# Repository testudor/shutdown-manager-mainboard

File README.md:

# Shutdown Manager Mainboard

This is a board for switching the AC mains input in machines such as 3D printers or CNC machines.

It is designed to be controlled by a push button switch with built-in dual color LEDs. An on-board LED driver controls these LEDs and different light patterns indicate the current system status.

The board has connections for two "nodes". These are external devices that require a safe shutdown procedure, such as a Raspberry Pi. It will trigger a shutdown of the nodes and will not turn off the power until they have completely shut down.

It is specifically designed to handle high inrush currents from SMPSs, which can cause normal relays to have their contacts weld together.

## I/O

### Nodes

| Pin | Function                                                                                     |
|-----|----------------------------------------------------------------------------------------------|
| NSD | Node Shutdown - is repeatedly cycled low and high to trigger a shutdown of external devices  |
| NHB | Node Heart Beat - should be driven HIGH, when a node is running and LOW when it's shut down. |

For an easy way to connect a Raspberry Pi see [this repo.](https://github.com/testudor/shutdown-manager-rpi-node)

### Push button switch

| Pin     | Function                                   |
|---------|--------------------------------------------|
| SW-/SW+ | Connected to the power switch.             |
| LD1/LD2 | Connected to the switches' dual color LED. |

I can recommend the ONPOW GQ19F-10E/RG/12/S, however any push button switch with 12V dual color LEDs should work. By dual color I mean LEDs which change their color based on polarity.

## Assembly

All necessary files can be found in the release section. They are compatible with the usual fab houses.

To use the full 16A this board was designed for, get 2oz PCBs or liberally coat the mains voltage traces on the bottom in solder.

I'm leaving these instructions intentionally vague as this is *NOT* a beginner's project. The more experienced should know what to do.

## Firmware

This board requires firmware to be flashed and configured. For details see [this repo.](https://github.com/testudor/shutdown-manager-firmware)

## Disclaimer

**WARNING:**

This board was designed to the best of my knowledge, but I am *NOT* an electrical engineer. If you decide to build this, I am not liable for damages or harm to yourself or anyone else.

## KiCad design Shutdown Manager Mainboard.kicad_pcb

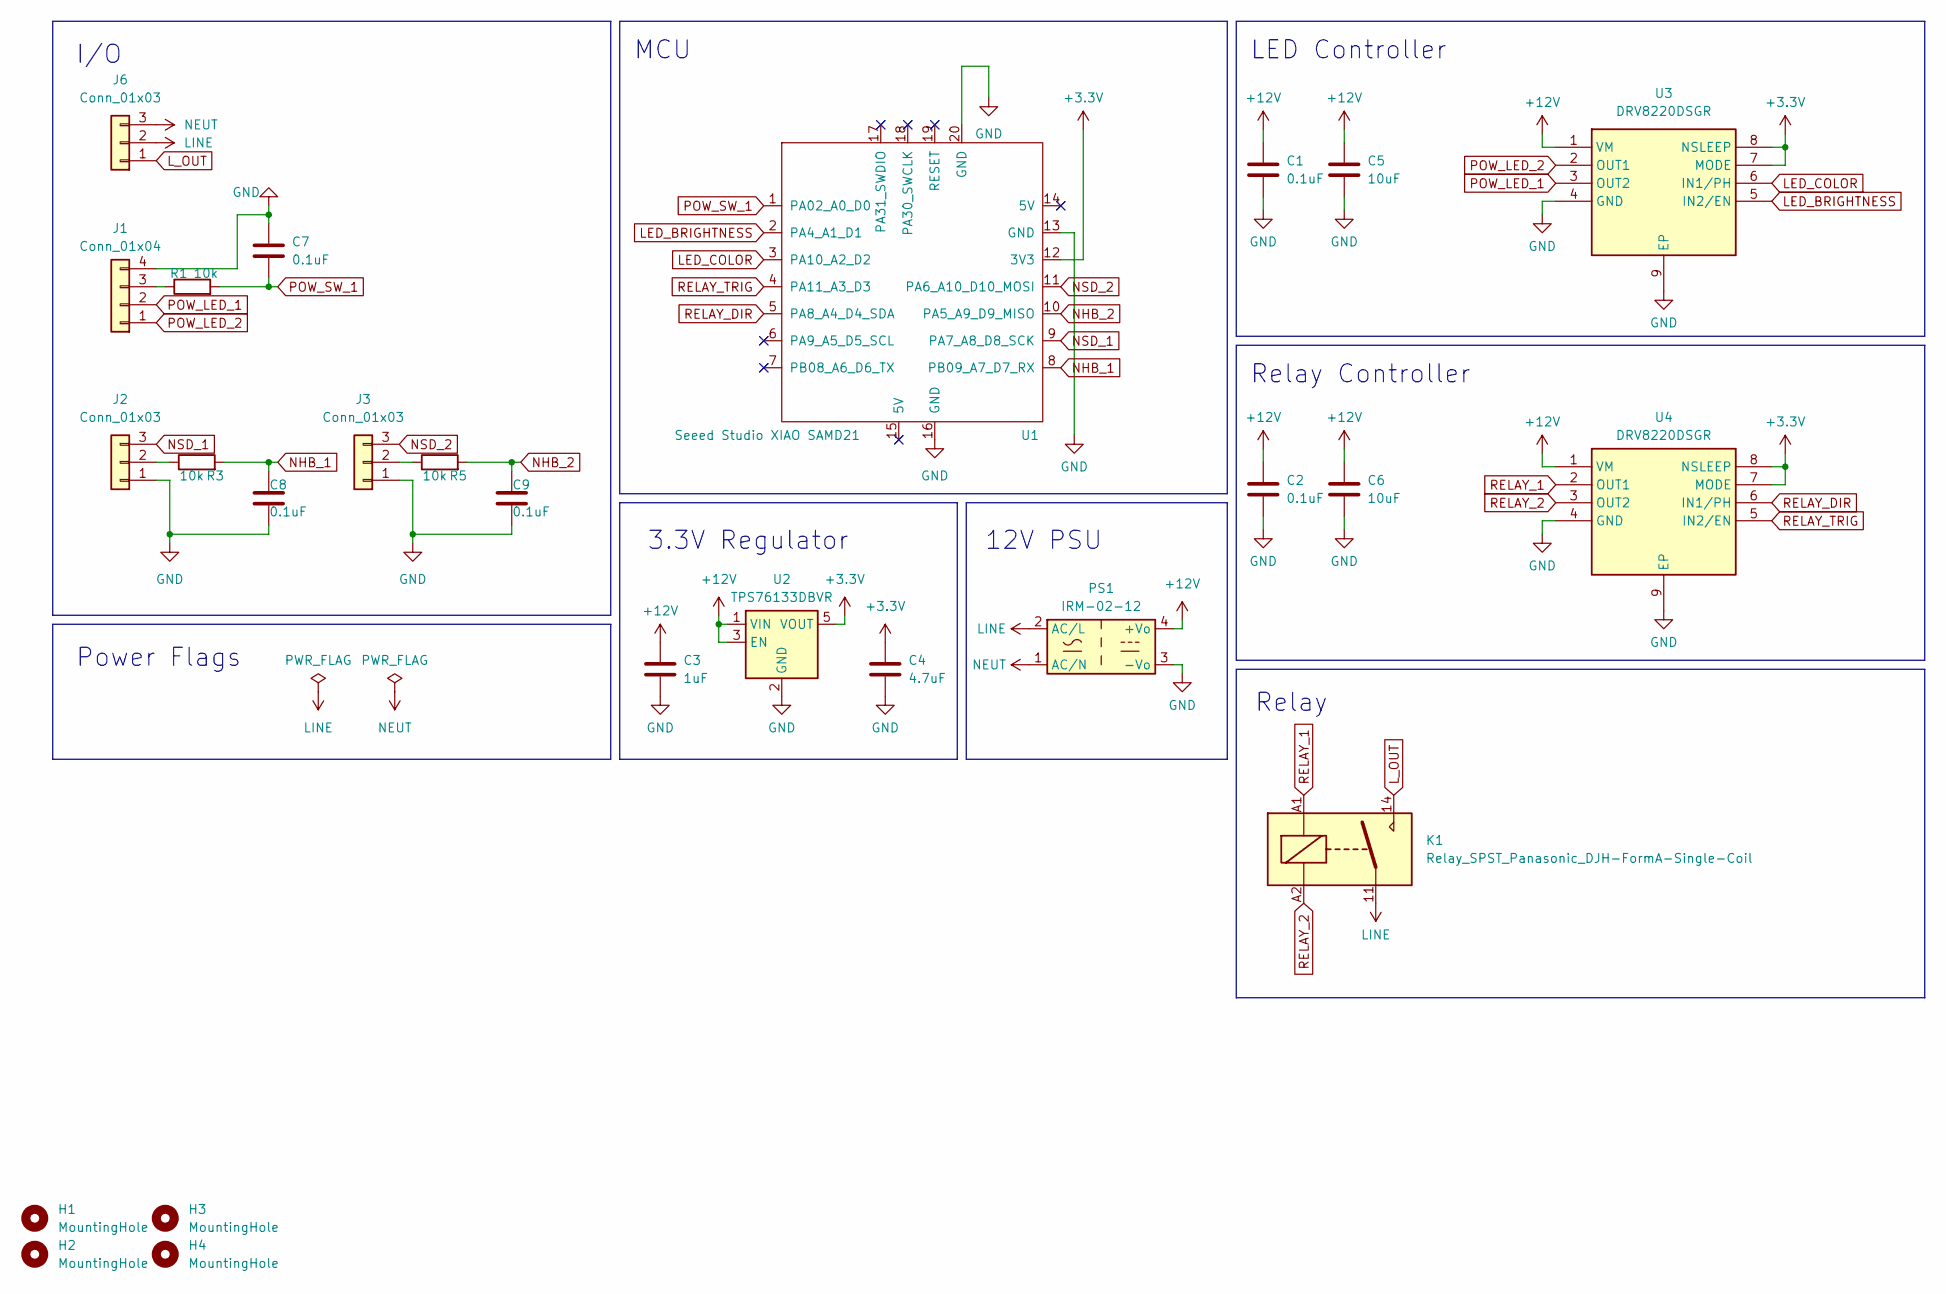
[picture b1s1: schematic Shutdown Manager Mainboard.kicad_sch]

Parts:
C1, C2, C7, C8, C9: 0.1uF; C_0402_1005Metric; MPN C1525
C3: 1uF; C_0402_1005Metric; MPN C52923
C4: 4.7uF; C_0603_1608Metric; MPN C19666
C5, C6: 10uF; C_0603_1608Metric; MPN C96446
H1, H2, H3, H4: MountingHole; MountingHole_3.2mm_M3_ISO7380_Pad_TopBottom
J1: Conn_01x04; JST_XH_B4B-XH-A_1x04_P2.50mm_Vertical; MPN C722867
J2, J3: Conn_01x03; JST_XH_B3B-XH-A_1x03_P2.50mm_Vertical; MPN C722863
J6: Conn_01x03; 282844-3; MPN C591951
K1: Relay_SPST_Panasonic_DJH-FormA-Single-Coil
PS1: IRM-02-12; Converter_ACDC_MeanWell_IRM-02-xx_THT
R1, R3, R5: 10k; R_0402_1005Metric; MPN C25744
U1: Seeed Studio XIAO SAMD21; XIAO-SAMD21-RP2040-14P-2.54-21X17.8MM (Seeeduino XIAO)
U2: TPS76133DBVR; SOT-23-5; MPN C194885
U3, U4: DRV8220DSGR; WSON-8-1EP_2x2mm_P0.5mm_EP0.9x1.6mm; Manufacturer_Part_Number DRV8220DSGR; Mouser Part Number 595-DRV8220DSGR

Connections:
+3.3V: C4.1, U1.12 (3V3), U2.5 (VOUT), U3.7 (MODE), U3.8 (NSLEEP), U4.7 (MODE), U4.8 (NSLEEP)
+12V: C1.1, C2.1, C3.1, C5.1, C6.1, PS1.4 (+Vo), U2.1 (VIN), U2.3 (EN), U3.1 (VM), U4.1 (VM)
GND: C1.2, C2.2, C3.2, C4.2, C5.2, C6.2, C7.1, C8.2, C9.2, J1.4, J2.1, J3.1, PS1.3 (-Vo), U1.13 (GND), U1.16 (GND), U1.20 (GND), U2.2 (GND), U3.4 (GND), U3.9 (EP), U4.4 (GND), U4.9 (EP)
LED_BRIGHTNESS: U1.2 (PA4_A1_D1), U3.5 (IN2/EN)
LED_COLOR: U1.3 (PA10_A2_D2), U3.6 (IN1/PH)
LINE: J6.2, K1.11, PS1.2 (AC/L)
L_OUT: J6.1, K1.14
NEUT: J6.3, PS1.1 (AC/N)
NHB_1: C8.1, R3.2, U1.8 (PB09_A7_D7_RX)
NHB_2: C9.1, R5.2, U1.10 (PA5_A9_D9_MISO)
NSD_1: J2.3, U1.9 (PA7_A8_D8_SCK)
NSD_2: J3.3, U1.11 (PA6_A10_D10_MOSI)
unnamed: J1.3, R1.1
unnamed: J2.2, R3.1
unnamed: J3.2, R5.1
POW_LED_1: J1.2, U3.3 (OUT2)
POW_LED_2: J1.1, U3.2 (OUT1)
POW_SW_1: C7.2, R1.2, U1.1 (PA02_A0_D0)
RELAY_1: K1.A1, U4.2 (OUT1)
RELAY_2: K1.A2, U4.3 (OUT2)
RELAY_DIR: U1.5 (PA8_A4_D4_SDA), U4.6 (IN1/PH)
RELAY_TRIG: U1.4 (PA11_A3_D3), U4.5 (IN2/EN)

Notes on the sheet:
Relay
MCU
12V PSU
3.3V Regulator
LED Controller
Relay Controller
Power Flags
I/O

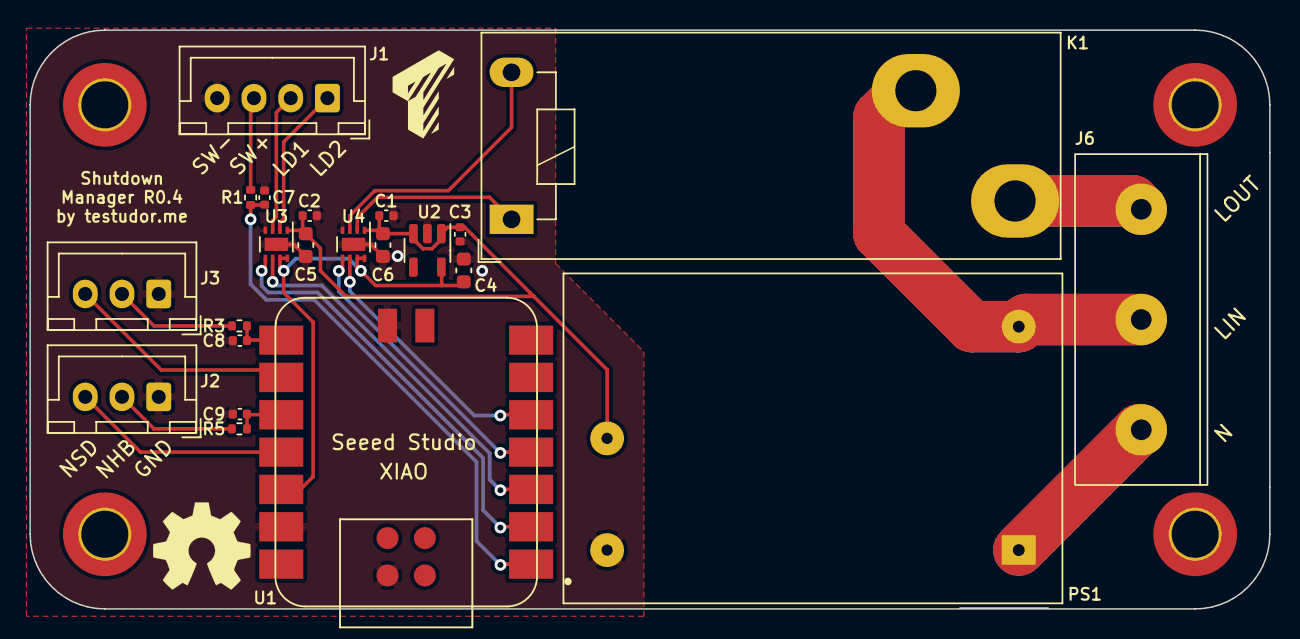
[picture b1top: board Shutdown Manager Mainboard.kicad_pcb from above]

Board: 2 copper layers, 84.3 x 39.4 mm, 26 parts (0 on the bottom side), 22 nets.

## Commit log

2023-11-29 Added strong external pullup/-down resistors to inputs, Added RC filter to main power button input
2023-11-30 intial readme draft
2024-02-07 Fixed heartbeat input filtering
